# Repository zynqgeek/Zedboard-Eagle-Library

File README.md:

Zedboard-Eagle-Library
======================

Zedboard Eagle Library

This library constants schematic symbols and layout drawings for useful connectors to interface with the Zedboard from Avnet Electronics.  This library has not been tested by it's author(s) and comes with no guarantee.  This library nor it's author(s) have no affiliations with Avnet, Xilinx, or Digilent Inc.

The library includes:

LPC FMC
    The Low Pin Count FPGA Mezzanine Connector that is including on the Zedboard is male.  This library has the female counterpart to this connector.

XADC
    There is an XADC connector including in this library that is identical to that found on the Zedboard (and other Xilinx 7-Series FPGA boards).  The connector is intended to be used in conjunction with a ribbon cable between the Zedboard and the custom board with this connector on it.

PMOD
    It was the decision of the author(s) of this library not to include a PMOD schematic symbol or layout drawing due to the strict rules associated with the PMOD standard.  It is in no way out goal to promote the mis-use of standards, and due to it's complexity it was not included.  Please see the full PMOD standard here: http://www.digilentinc.com/Pmods/Digilent-Pmod_%20Interface_Specification.pdf

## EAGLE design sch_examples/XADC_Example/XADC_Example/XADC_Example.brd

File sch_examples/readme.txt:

This folder contains different examples using the devices that are included within the Zedboard Eagle Library.

These schematics come with no guarantee and have not been tested.  They should be used as a reference.

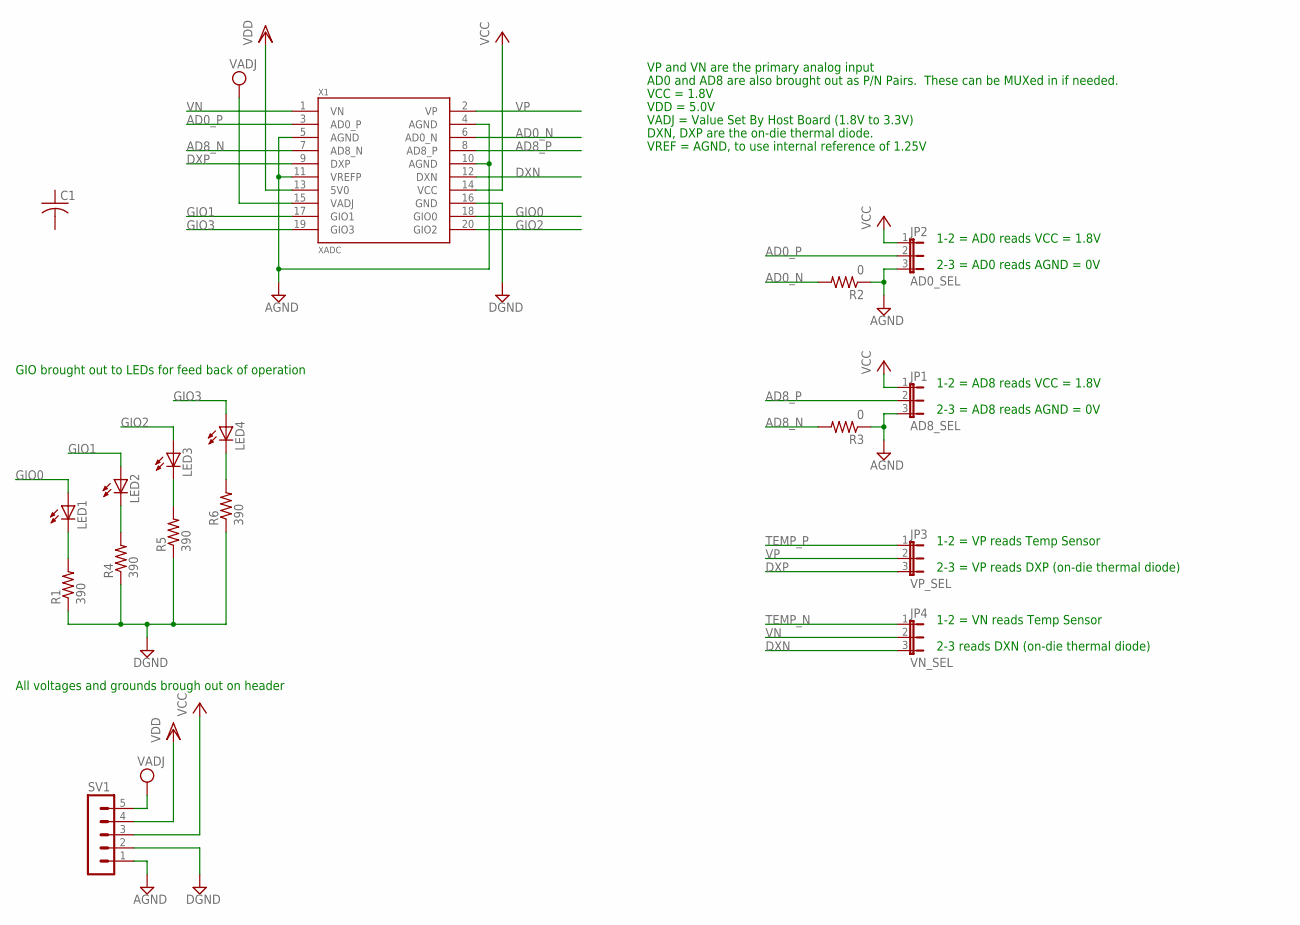
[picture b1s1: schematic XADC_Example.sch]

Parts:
C1: C-USC0603; C0603
JP1: AD8_SEL; JP2
JP2: AD0_SEL; JP2
JP3: VP_SEL; JP2
JP4: VN_SEL; JP2
LED1, LED2, LED3, LED4: LED5MM
R1, R4, R5, R6: 390; R0603
R2, R3: 0; R0603
SV1: MA05-1
X1: XADC; XADC_2X10

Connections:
AD0_N: R2.2, X1.6 (AD0_N)
AD0_P: JP2.2, X1.3 (AD0_P)
AD8_N: R3.2, X1.7 (AD8_N)
AD8_P: JP1.2, X1.8 (AD8_P)
AGND: JP1.3, JP2.3, R2.1, R3.1, SV1.1, X1.4 (AGND), X1.5 (AGND), X1.10 (AGND), X1.11 (VREFP)
DGND: R1.1, R4.1, R5.1, R6.1, SV1.2, X1.16 (GND)
DXN: JP4.3, X1.12 (DXN)
DXP: JP3.3, X1.9 (DXP)
GIO0: LED1.A, X1.18 (GIO0)
GIO1: LED2.A, X1.17 (GIO1)
GIO2: LED3.A, X1.20 (GIO2)
GIO3: LED4.A, X1.19 (GIO3)
unnamed: LED1.K (C), R1.2
unnamed: LED2.K (C), R4.2
unnamed: LED3.K (C), R5.2
unnamed: LED4.K (C), R6.2
TEMP_N: JP4.1
TEMP_P: JP3.1
VCC: JP1.1, JP2.1, SV1.3, X1.14 (VCC)
VDD: SV1.4, SV1.5, X1.13 (5V0), X1.15 (VADJ)
VN: JP4.2, X1.1 (VN)
VP: JP3.2, X1.2 (VP)

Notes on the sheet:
VP and VN are the primary analog input
AD0 and AD8 are also brought out as P/N Pairs. These can be MUXed in if needed.
VCC = 1.8V
VDD = 5.0V
VADJ = Value Set By Host Board (1.8V to 3.3V)
DXN, DXP are the on-die thermal diode.
1-2 = AD0 reads VCC = 1.8V
2-3 = AD0 reads AGND = 0V
1-2 = AD8 reads VCC = 1.8V
2-3 = AD8 reads AGND = 0V
2-3 = VP reads DXP (on-die thermal diode)
1-2 = VP reads Temp Sensor
1-2 = VN reads Temp Sensor
2-3 reads DXN (on-die thermal diode)
VREF = AGND, to use internal reference of 1.25V
All voltages and grounds brough out on header
GIO brought out to LEDs for feed back of operation

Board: 2 copper layers, 17 parts (0 on the bottom side), 20 nets, no tracks yet.

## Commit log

2012-07-16 Initial commit. Holds FPGA Mezzanine Card (FMC) Low Pin Count (LPC) connector as well as XADC connector (to be used with ribbon cable).
2012-07-16 Added content to README file. Described different connectors and their intended use.
2012-07-23 Initial commit for the XADC schematic example. Note: THIS IS NOT FINISHED! Committing to show progress. Need to add temperature sensor and route board.
2012-07-23 initial commit for readme file.
